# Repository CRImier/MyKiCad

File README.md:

# My KiCad PCBs

This is a repository where I upload [almost] everything that I design in KiCad.
As usual, if you think your work warrants doing backups, just upload it to a git repo ;-P
I hope this will be useful.

About 50% of all of the PCBs have a README describing what they're meant for and
the PCBs physical parameters, the README follows the TEMPLATE.md standard. I'll be
adding more READMEs as I go.

If you need gerbers, you have to plot them yourself by opening the KiCad PCB file
(quick to do with `pcbnew file.kicad_pcb`) and using the File=>Plot dialog.
Majority of the projects already have reasonable export settings, just like I intended.

Same goes for schematic PDFs - if you need them, export them yourself. Adding gerber and sch
files to this repo would be a problem. I might decide to abuse GitHub releases for that eventually,
though.

At some point, hopefully, I'll make a good workflow to also add pictures to READMEs.

Scripts:

- `make_gml.py` - creates .gml files in gerber folders by copying the .gm1 files. Useful for ThisIsNotRocketScience GerberPanelizer.
- `check_kicad5_files.py` - shows you directories which have new Kicad6 kicad_pro and kicad_sch files but still contain old sch and pro files
- `stats.sh` - shows PCB file and README file counts for gamification purposes

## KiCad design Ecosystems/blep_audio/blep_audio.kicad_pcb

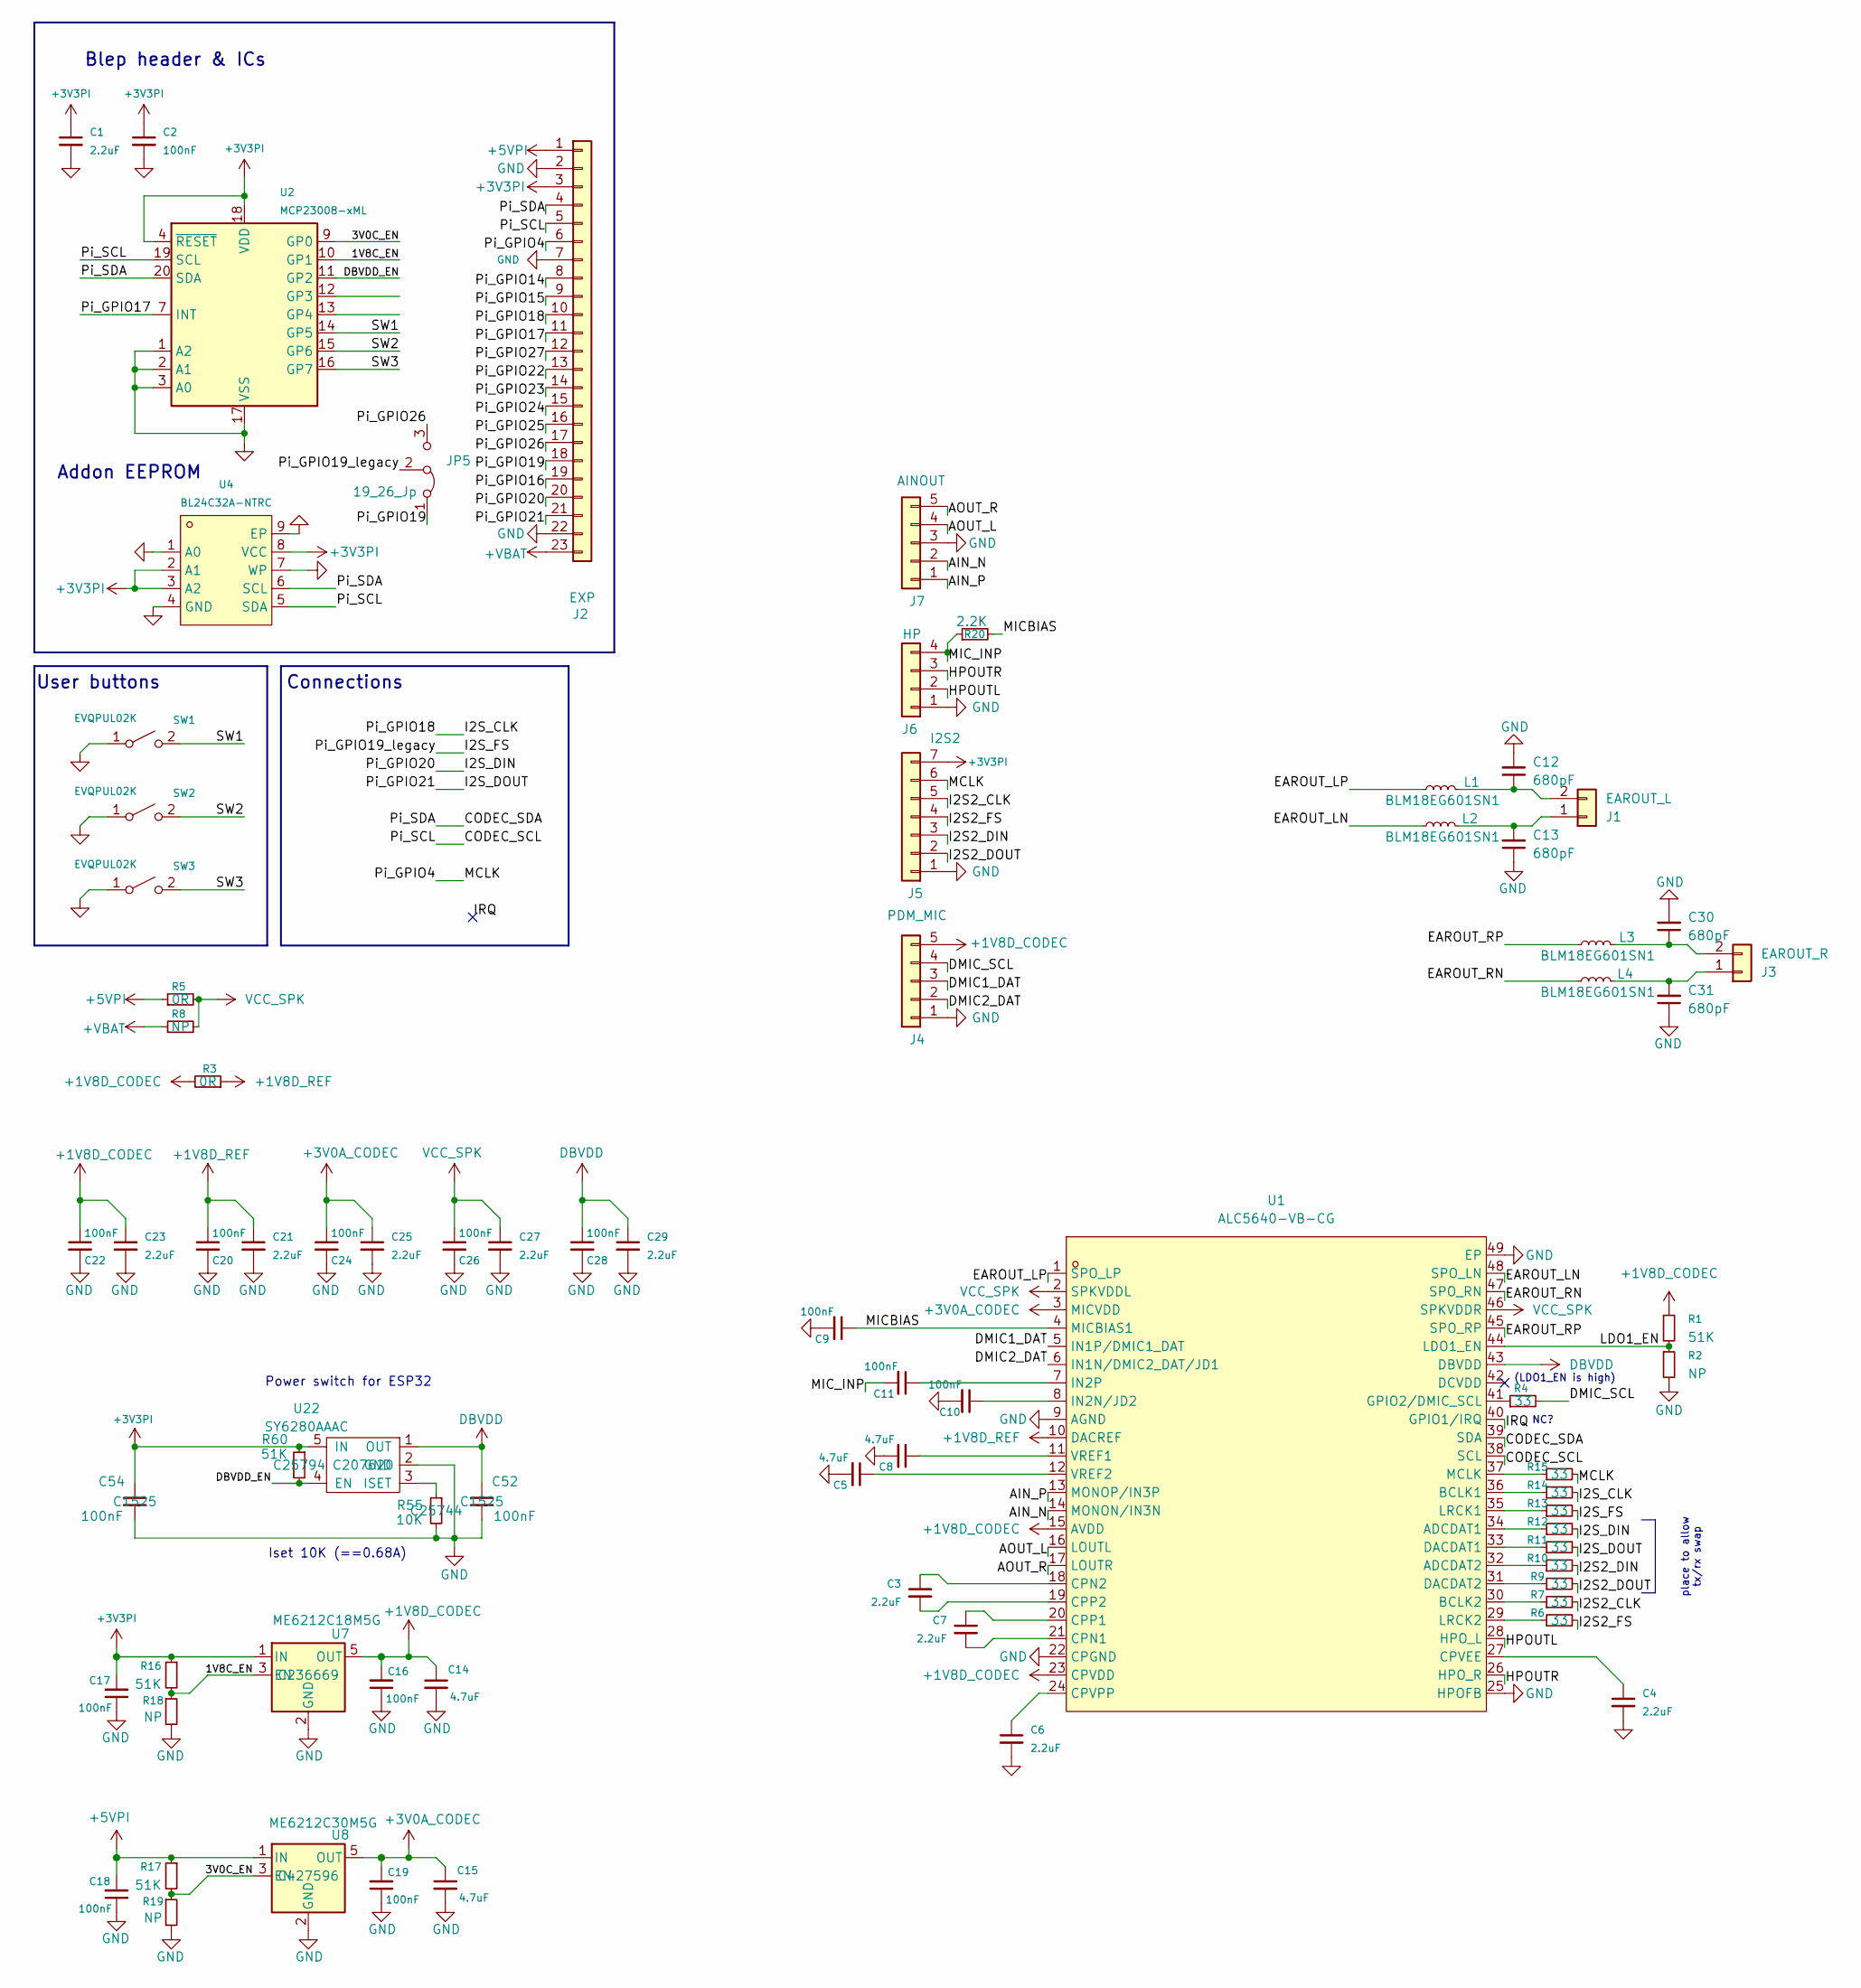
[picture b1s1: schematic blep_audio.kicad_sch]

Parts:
C1, C3, C4, C6, C7, C21, C23, C25, C27, C29: 2.2uF; C_0402_1005Metric
C2, C9, C10, C11, C16, C17, C18, C19, C20, C22, C24, C26, C28: 100nF; C_0402_1005Metric; lcsc_id C1525
C5, C8, C14, C15: 4.7uF; C_0402_1005Metric
C12, C13, C30, C31: 680pF; C_0402_1005Metric
C52, C54: 100nF; C_0402_1005Metric; LCSC Part C1525
J1: EAROUT_L; PinHeader_1x02_P2.54mm_Vertical
J2: EXP; PinHeader_1x23_P2.54mm_Vertical
J3: EAROUT_R; PinHeader_1x02_P2.54mm_Vertical
J4: PDM_MIC; PinHeader_1x05_P2.54mm_Vertical
J5: I2S2; PinHeader_1x07_P2.54mm_Vertical
J6: HP; PinHeader_1x04_P2.54mm_Vertical
J7: AINOUT; PinHeader_1x05_P2.54mm_Vertical
JP5: 19_26_Jp; SolderJumper-3_P1.3mm_Bridged2Bar12_RoundedPad1.0x1.5mm_Num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
L1, L2, L3, L4: BLM18EG601SN1; L_0603_1608Metric
R1, R16, R17: 51K; R_0402_1005Metric
R2, R8, R18, R19: NP; R_0402_1005Metric
R3, R5: 0R; R_0402_1005Metric
R4, R6, R7, R9, R10, R11, R12, R13, R14, R15: 33; R_0402_1005Metric
R20: 2.2K; R_0402_1005Metric
R55: 10K; R_0402_1005Metric; LCSC Part C25744
R60: 51K; R_0402_1005Metric; LCSC Part C25794
SW1, SW2, SW3: EVQPUL02K; Panasonic_EVQPUL_EVQPUC
U1: ALC5640-VB-CG; QFN-48-1EP_6x6mm_P0.4mm_EP4.4x4.4mm; LCSC Part C472491
U2: MCP23008-xML; QFN-20-1EP_4x4mm_P0.5mm_EP2.7x2.7mm
U4: BL24C32A-NTRC; DFN-8_L3.0-W2.0-P0.50-BL-EP; LCSC Part C691878
U7: ME6212C18M5G; SOT-23-5; LCSC Part C236669
U8: ME6212C30M5G; SOT-23-5; LCSC Part C427596
U22: SY6280AAAC; SOT-23-5; LCSC Part C207620

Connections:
+1V8D_CODEC: C14.1, C16.2, C22.1, C23.1, J4.5, R1.1, R3.2, U1.15 (AVDD), U1.23 (CPVDD), U7.5 (OUT)
+1V8D_REF: C20.1, C21.1, R3.1, U1.10 (DACREF)
+3V0A_CODEC: C15.1, C19.2, C24.1, C25.1, U1.3 (MICVDD), U8.5 (OUT)
+3V3PI: C1.1, C2.1, C17.2, C54.1, J2.3, J5.7, R16.1, R60.1, U2.4 (~RESET), U2.18 (VDD), U4.2 (A1), U4.3 (A2), U4.8 (VCC), U7.1 (IN), U22.5 (IN)
+5VPI: C18.2, J2.1, R5.1, R17.1, U8.1 (IN)
+VBAT: J2.23, R8.1
/1V8C_EN: R16.2, R18.1, U2.10 (GP1), U7.3 (EN)
/3V0C_EN: R17.2, R19.1, U2.9 (GP0), U8.3 (EN)
/AIN_N: J7.2, U1.14 (MONON/IN3N)
/AIN_P: J7.1, U1.13 (MONOP/IN3P)
/AOUT_L: J7.4, U1.16 (LOUTL)
/AOUT_R: J7.5, U1.17 (LOUTR)
/CODEC_SCL: J2.5, U1.38 (SCL), U2.19 (SCL), U4.5 (SDA)
/CODEC_SDA: J2.4, U1.39 (SDA), U2.20 (SDA), U4.6 (SCL)
/DBVDD_EN: R60.2, U2.11 (GP2), U22.4 (EN)
/DMIC1_DAT: J4.3, U1.5 (IN1P/DMIC1_DAT)
/DMIC2_DAT: J4.2, U1.6 (IN1N/DMIC2_DAT/JD1)
/DMIC_SCL: J4.4, R4.2
/EAROUT_LN: L2.1, U1.48 (SPO_LN)
/EAROUT_LP: L1.1, U1.1 (SPO_LP)
/EAROUT_RN: L4.1, U1.47 (SPO_RN)
/EAROUT_RP: L3.1, U1.45 (SPO_RP)
/HPOUTL: J6.2, U1.28 (HPO_L)
/HPOUTR: J6.3, U1.26 (HPO_R)
/I2S2_CLK: J5.5, R7.2
/I2S2_DIN: J5.3, R10.2
/I2S2_DOUT: J5.2, R9.2
/I2S2_FS: J5.4, R6.2
/I2S_CLK: J2.10, R14.2
/I2S_DIN: J2.20, R12.2
/I2S_DOUT: J2.21, R11.2
/I2S_FS: JP5.2 (C), R13.2
/IRQ: U1.40 (GPIO1/IRQ)
/LDO1_EN: R1.2, R2.1, U1.44 (LDO1_EN)
/MCLK: J2.6, J5.6, R15.2
/MICBIAS: C9.1, R20.2, U1.4 (MICBIAS1)
/MIC_INP: C11.2, J6.4, R20.1
/Pi_GPIO14: J2.8
/Pi_GPIO15: J2.9
/Pi_GPIO16: J2.19
/Pi_GPIO17: J2.11, U2.7 (INT)
/Pi_GPIO19: J2.18, JP5.1 (A)
/Pi_GPIO22: J2.13
/Pi_GPIO23: J2.14
/Pi_GPIO24: J2.15
/Pi_GPIO25: J2.16
/Pi_GPIO26: J2.17, JP5.3 (B)
/Pi_GPIO27: J2.12
/SW1: SW1.2 (B), U2.14 (GP5)
/SW2: SW2.2 (B), U2.15 (GP6)
/SW3: SW3.2 (B), U2.16 (GP7)
DBVDD: C28.1, C29.1, C52.1, U1.43 (DBVDD), U22.1 (OUT)
GND: C1.2, C2.2, C4.2, C5.2, C6.2, C8.2, C9.2, C10.2, C12.2, C13.1, C14.2, C15.2, C16.1, C17.1, C18.1, C19.1, C20.2, C21.2, C22.2, C23.2, C24.2, C25.2, C26.2, C27.2, C28.2, C29.2, C30.2, C31.1, C52.2, C54.2, J2.2, J2.7, J2.22, J4.1, J5.1, J6.1, J7.3, R2.2, R18.2, R19.2, R55.2, SW1.1 (A), SW2.1 (A), SW3.1 (A), U1.9 (AGND), U1.22 (CPGND), U1.25 (HPOFB), U1.49 (EP), U2.1 (A2), U2.2 (A1), U2.3 (A0), U2.17 (VSS), U4.1 (A0), U4.4 (GND), U4.7 (WP), U4.9 (EP), U7.2 (GND), U8.2 (GND), U22.2 (GND)
unnamed: C13.2, J1.1, L2.2
unnamed: C12.1, J1.2, L1.2
unnamed: C31.2, J3.1, L4.2
unnamed: C30.1, J3.2, L3.2
unnamed: R12.1, U1.34 (ADCDAT1)
unnamed: R10.1, U1.32 (ADCDAT2)
unnamed: R14.1, U1.36 (BCLK1)
unnamed: R7.1, U1.30 (BCLK2)
unnamed: C7.2, U1.21 (CPN1)
unnamed: C3.1, U1.18 (CPN2)
unnamed: C7.1, U1.20 (CPP1)
unnamed: C3.2, U1.19 (CPP2)
unnamed: C4.1, U1.27 (CPVEE)
unnamed: C6.1, U1.24 (CPVPP)
unnamed: R11.1, U1.33 (DACDAT1)
unnamed: R9.1, U1.31 (DACDAT2)
unnamed: R4.1, U1.41 (GPIO2/DMIC_SCL)
unnamed: C10.1, U1.8 (IN2N/JD2)
unnamed: C11.1, U1.7 (IN2P)
unnamed: R13.1, U1.35 (LRCK1)
unnamed: R6.1, U1.29 (LRCK2)
unnamed: R15.1, U1.37 (MCLK)
unnamed: C8.1, U1.11 (VREF1)
unnamed: C5.1, U1.12 (VREF2)
unnamed: R55.1, U22.3 (ISET)
VCC_SPK: C26.1, C27.1, R5.2, R8.2, U1.2 (SPKVDDL), U1.46 (SPKVDDR)

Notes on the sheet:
Addon EEPROM
place to allow tx/rx swap
Power switch for ESP32
Connections
NC?
User buttons
Blep header & ICs
Iset 10K (==0.68A)
(LDO1_EN is high)

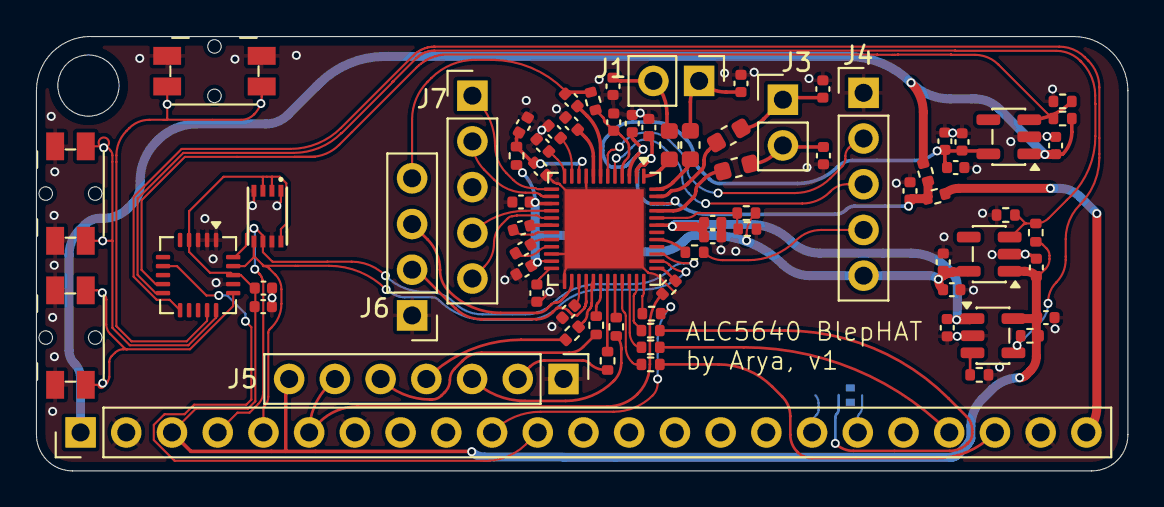
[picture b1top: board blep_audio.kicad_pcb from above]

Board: 2 copper layers, 60.6 x 24.1 mm, 76 parts (1 on the bottom side), 70 nets.

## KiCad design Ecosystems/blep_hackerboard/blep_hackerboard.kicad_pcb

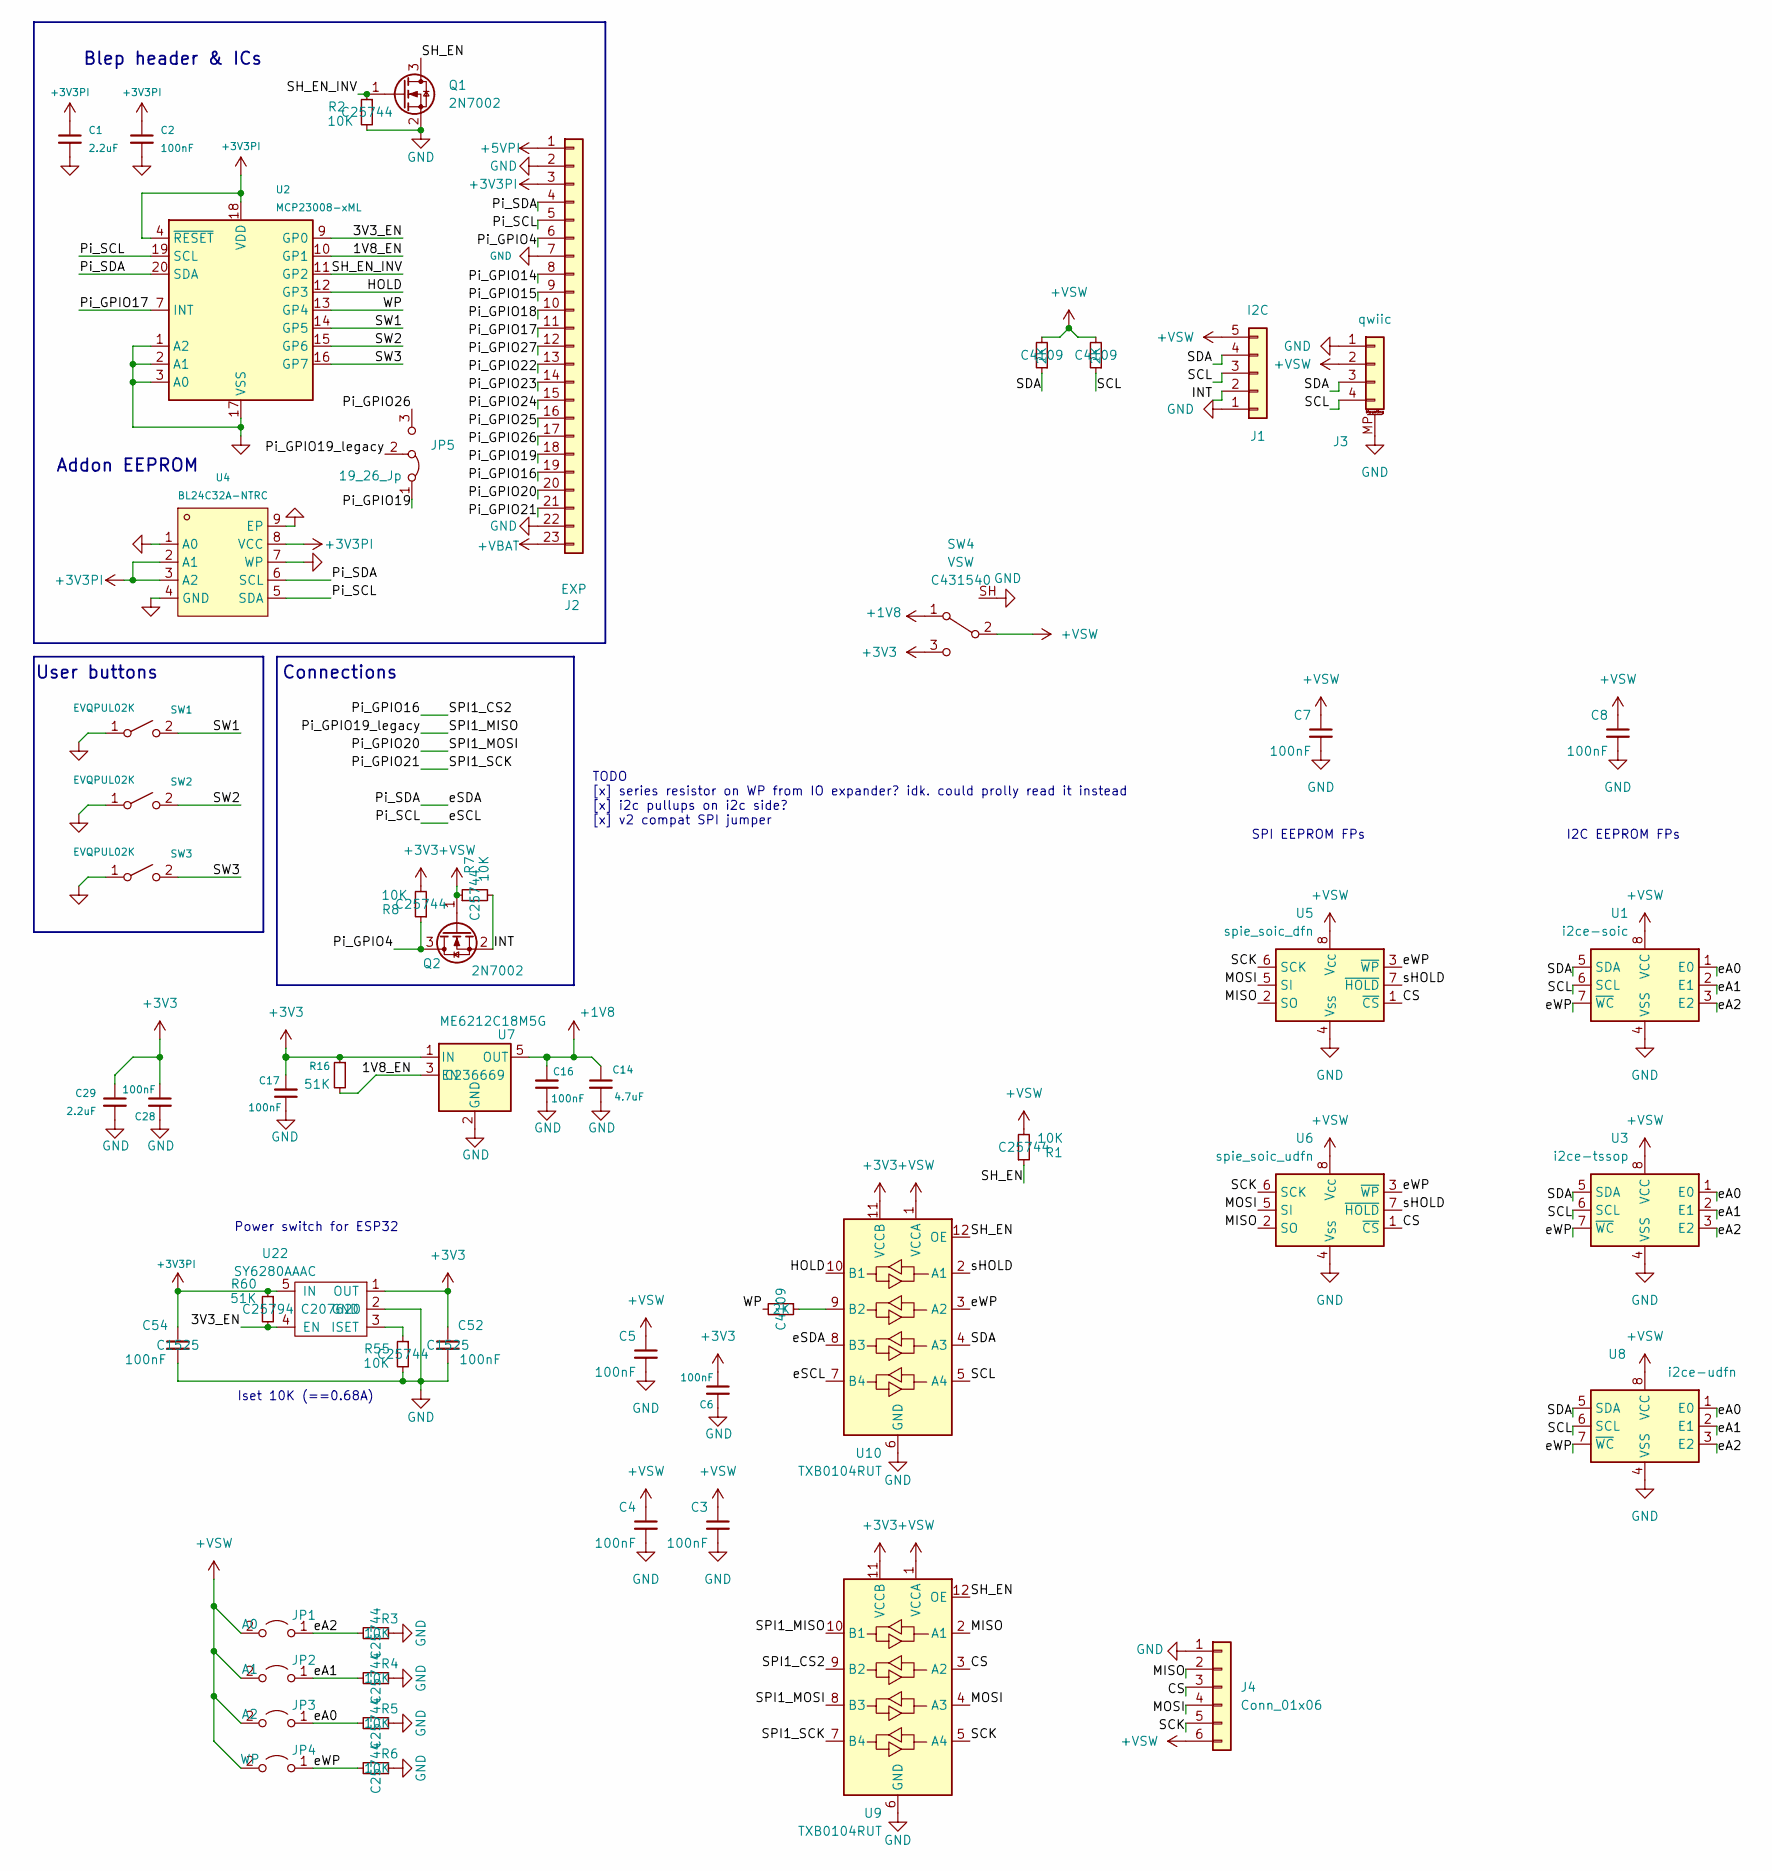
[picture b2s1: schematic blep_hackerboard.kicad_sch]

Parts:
C1, C29: 2.2uF; C_0402_1005Metric
C2, C3, C4, C5, C6, C7, C8, C16, C17, C28: 100nF; C_0402_1005Metric; lcsc_id C1525
C14: 4.7uF; C_0402_1005Metric
C52, C54: 100nF; C_0402_1005Metric; LCSC Part C1525
J1: I2C; PinHeader_1x05_P2.54mm_Vertical
J2: EXP; PinHeader_1x23_P2.54mm_Vertical
J3: qwiic; JST_SH_SM04B-SRSS-TB_1x04-1MP_P1.00mm_Horizontal
J4: Conn_01x06; PinHeader_1x06_P2.54mm_Vertical
JP1: A0; jumper_smol
JP2: A1; jumper_smol
JP3: A2; jumper_smol
JP4: WP; jumper_smol
JP5: 19_26_Jp; SolderJumper-3_P1.3mm_Bridged2Bar12_RoundedPad1.0x1.5mm_Num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
Q1, Q2: 2N7002; SOT-23
R1, R2, R3, R4, R5, R6, R7, R8, R55: 10K; R_0402_1005Metric; LCSC Part C25744
R9, R10, R116: 2K; R_0402_1005Metric; LCSC Part C4109
R16: 51K; R_0402_1005Metric
R60: 51K; R_0402_1005Metric; LCSC Part C25794
SW1, SW2, SW3: EVQPUL02K; Panasonic_EVQPUL_EVQPUC
SW4: VSW; SW_SPDT_PCM12_SH; LCSC Part C431540
U1: i2ce-soic; SOIC-8_3.9x4.9mm_P1.27mm
U2: MCP23008-xML; QFN-20-1EP_4x4mm_P0.5mm_EP2.7x2.7mm
U3: i2ce-tssop; TSSOP-8_4.4x3mm_P0.65mm
U4: BL24C32A-NTRC; DFN-8_L3.0-W2.0-P0.50-BL-EP; LCSC Part C691878
U5: spie_soic_dfn; SOIC-8W_5.3x5.3mm_P1.27mm
U6: spie_soic_udfn; DFN-8-1EP_3x2mm_P0.5mm_EP1.3x1.5mm
U7: ME6212C18M5G; SOT-23-5; LCSC Part C236669
U8: i2ce-udfn; DFN-8-1EP_3x2mm_P0.5mm_EP1.3x1.5mm
U9, U10: TXB0104RUT; Texas_R-PUQFN-N12
U22: SY6280AAAC; SOT-23-5; LCSC Part C207620

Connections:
+1V8: C14.1, C16.2, SW4.1 (A), U7.5 (OUT)
+3V3: C6.1, C17.2, C28.1, C29.1, C52.1, R8.2, R16.1, SW4.3 (C), U7.1 (IN), U9.11 (VCCB), U10.11 (VCCB), U22.1 (OUT)
+3V3PI: C1.1, C2.1, C54.1, J2.3, R60.1, U2.4 (~RESET), U2.18 (VDD), U4.2 (A1), U4.3 (A2), U4.8 (VCC), U22.5 (IN)
+5VPI: J2.1
+VBAT: J2.23
+VSW: C3.1, C4.1, C5.1, C7.1, C8.1, J1.5, J3.2, J4.6, JP1.2 (B), JP2.2 (B), JP3.2 (B), JP4.2 (B), Q2.1 (G), R1.2, R7.1, R9.2, R116.2, SW4.2 (B), U1.8 (VCC), U3.8 (VCC), U5.8 (V_{CC}), U6.8 (V_{CC}), U8.8 (VCC), U9.1 (VCCA), U10.1 (VCCA)
/1V8_EN: R16.2, U2.10 (GP1), U7.3 (EN)
/3V3_EN: R60.2, U2.9 (GP0), U22.4 (EN)
/CS: J4.3, U5.1 (~CS), U6.1 (~CS), U9.3 (A2)
/HOLD: U2.12 (GP3), U10.10 (B1)
/INT: J1.2, Q2.2 (S), R7.2
/MISO: J4.2, U5.2 (SO), U6.2 (SO), U9.2 (A1)
/MOSI: J4.4, U5.5 (SI), U6.5 (SI), U9.4 (A3)
/Pi_GPIO4: J2.6, Q2.3 (D), R8.1
/Pi_GPIO14: J2.8
/Pi_GPIO15: J2.9
/Pi_GPIO16: J2.19, U9.9 (B2)
/Pi_GPIO17: J2.11, U2.7 (INT)
/Pi_GPIO18: J2.10
/Pi_GPIO19: J2.18, JP5.1 (A)
/Pi_GPIO19_legacy: JP5.2 (C), U9.10 (B1)
/Pi_GPIO20: J2.20, U9.8 (B3)
/Pi_GPIO21: J2.21, U9.7 (B4)
/Pi_GPIO22: J2.13
/Pi_GPIO23: J2.14
/Pi_GPIO24: J2.15
/Pi_GPIO25: J2.16
/Pi_GPIO26: J2.17, JP5.3 (B)
/Pi_GPIO27: J2.12
/Pi_SCL: J2.5, U2.19 (SCL), U4.5 (SDA), U10.7 (B4)
/Pi_SDA: J2.4, U2.20 (SDA), U4.6 (SCL), U10.8 (B3)
/SCK: J4.5, U5.6 (SCK), U6.6 (SCK), U9.5 (A4)
/SCL: J1.3, J3.4, R9.1, U1.6 (SCL), U3.6 (SCL), U8.6 (SCL), U10.5 (A4)
/SDA: J1.4, J3.3, R116.1, U1.5 (SDA), U3.5 (SDA), U8.5 (SDA), U10.4 (A3)
/SH_EN: Q1.3 (D), R1.1, U9.12 (OE), U10.12 (OE)
/SH_EN_INV: Q1.1 (G), R2.1, U2.11 (GP2)
/SW1: SW1.2 (B), U2.14 (GP5)
/SW2: SW2.2 (B), U2.15 (GP6)
/SW3: SW3.2 (B), U2.16 (GP7)
/WP: R10.2, U2.13 (GP4)
/eA0: JP3.1 (A), R5.2, U1.1 (E0), U3.1 (E0), U8.1 (E0)
/eA1: JP2.1 (A), R4.2, U1.2 (E1), U3.2 (E1), U8.2 (E1)
/eA2: JP1.1 (A), R3.2, U1.3 (E2), U3.3 (E2), U8.3 (E2)
/eWP: JP4.1 (A), R6.2, U1.7 (~WC), U3.7 (~WC), U5.3 (~WP), U6.3 (~WP), U8.7 (~WC), U10.3 (A2)
/sHOLD: U5.7 (~HOLD), U6.7 (~HOLD), U10.2 (A1)
GND: C1.2, C2.2, C3.2, C4.2, C5.2, C6.2, C7.2, C8.2, C14.2, C16.1, C17.1, C28.2, C29.2, C52.2, C54.2, J1.1, J2.2, J2.7, J2.22, J3.1, J3.MP (MountPin), J4.1, Q1.2 (S), R2.2, R3.1, R4.1, R5.1, R6.1, R55.2, SW1.1 (A), SW2.1 (A), SW3.1 (A), SW4.SH, U1.4 (VSS), U2.1 (A2), U2.2 (A1), U2.3 (A0), U2.17 (VSS), U3.4 (VSS), U4.1 (A0), U4.4 (GND), U4.7 (WP), U4.9 (EP), U5.4 (V_{SS}), U6.4 (V_{SS}), U7.2 (GND), U8.4 (VSS), U9.6 (GND), U10.6 (GND), U22.2 (GND)
unnamed: R10.1, U10.9 (B2)
unnamed: R55.1, U22.3 (ISET)

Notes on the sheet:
Iset 10K (==0.68A)
Addon EEPROM
Power switch for ESP32
I2C EEPROM FPs
SPI EEPROM FPs
Connections
User buttons
TODO [x] series resistor on WP from IO expander? idk. could prolly read it instead [x] i2c pullups on i2c side? [x] v2 compat SPI jumper
Blep header & ICs

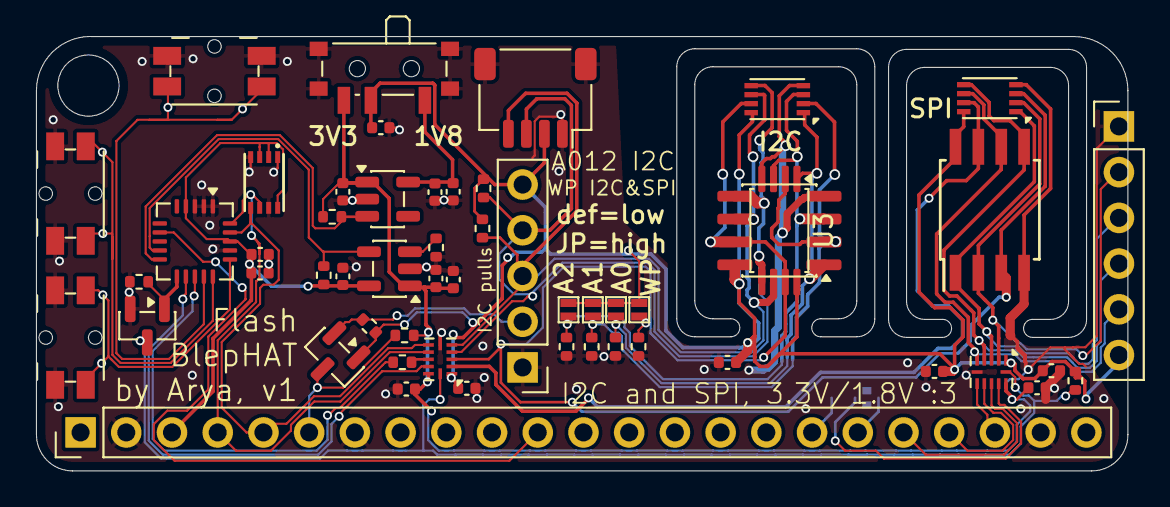
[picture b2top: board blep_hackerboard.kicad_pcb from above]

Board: 2 copper layers, 60.6 x 24.1 mm, 55 parts (1 on the bottom side), 38 nets.

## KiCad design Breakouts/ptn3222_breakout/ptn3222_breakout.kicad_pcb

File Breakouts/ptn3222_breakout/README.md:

# PTN3222 breakout

This is a breakout for the PTN3222, eUSB2 to USB2 converter and redriver chip, exposing as many of its features as possible
in the smallest possible footprint. PTN3222 can work in either of the two roles, with eUSB2 either facing host or device ports.
This board is designed to help you make use of any cool eUSB2 tech you might encounter in the future.

The PTN3222 is used for seemingly being the best bang for your buck, and being configurable without resistors.
TUSB2E22 is quite expensive and more bothersome to wireup,
and CYUSB2405 is apparently unobtainium; plus, both of these chips are dual-port.

All relevant pins are exposed on JST-SH connectors with QWIIC-style pinout, for ease of wireup.
All pinouts are silkscreened on the PCB, so you can wire it up manually if you wish, too.

I2C configuration should not be required for functioning in either of the two USB roles (datasheet page 10, at the top).
So, if you don't need I2C, feel free to omit R2, R4, Q1, and J3. That said, it's not clear to me that you can
safely omit R5 and R3 - watch out.

The board includes 5.1k pullups on the QWIIC I2C port, marked as R2 and R4.
I2C is translated to 3.3V by default, since the PTN3222 I2C port needs 1.8V from what I can tell,
and QWIIC standard requires 3.3V I2C.

PTN3222 ADDR is pulled to 1.8V with a 56k resistor. This should result in I2C address 0x47 (datasheet page 8).
Short JP1 to switch address to 0x4f, or short R1 to switch address to 0x43.

eUSB2's JST-SH connector's VCC pin is disconnected by default. This is done to avoid supplying 3.3V into 1.8V if eUSB and USB connectors
are mixed up, and also avoid accidentally supplying voltage into an eUSB2-carrying circuit without checking that the system can handle that voltage.
Solder the port's VCC switch jumper into your preferred position according to the system you'll use it in, or, alternatively, don't solder it at all.

eUSB2 and USB2 lines are not impedance-matched - this is a 2-layer board, USB2 is pretty robust, and the on-board distances are short.
They are, however, mostly skew-matched. USB2 and eUSB2 lines are ESD-protected by U3 (optional).

The USB-C port is not required for functioning. If you don't need it, feel free to DNP J4, R6-R9, as well as U4, C7, C8 (5V->3V3 reg).

If you know any other cool eUSB2 chips, please contact me and let me know!

## Images

## Notes

- Signal names are silkscreened on the board, top and bottom layers.
- This board is untested and there's no guarantees of fitness.
- I recommend a stencil for assembling this board.

## Info

- Software: Kicad 9
- Version: 1
- PCB size: 32x14mm
- Layer count: 2

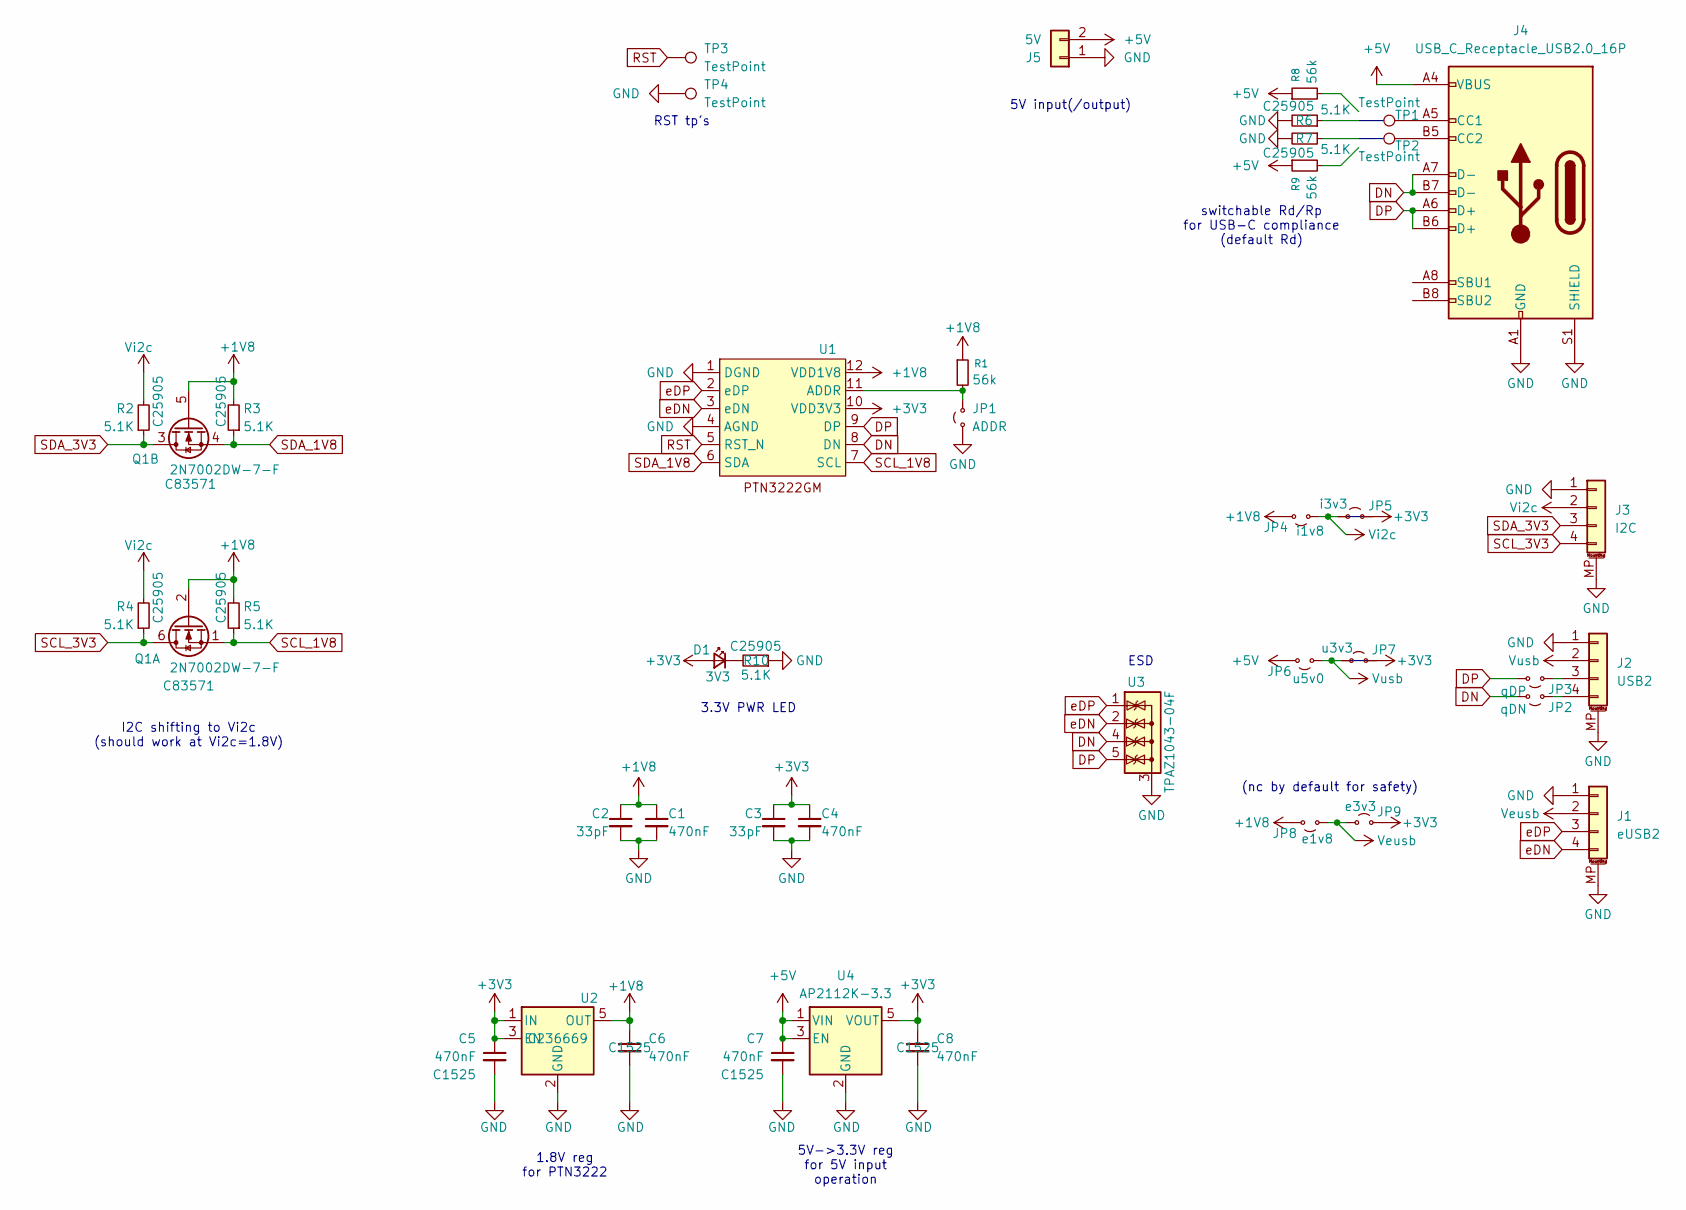
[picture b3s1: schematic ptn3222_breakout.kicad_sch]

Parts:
C1, C4: 470nF; C_0402_1005Metric
C2, C3: 33pF; C_0402_1005Metric
C5, C6, C7, C8: 470nF; C_0402_1005Metric; LCSC Part C1525
D1: 3V3; LED_0603_1608Metric
J1: eUSB2; JST_SH_SM04B-SRSS-TB_1x04-1MP_P1.00mm_Horizontal
J2: USB2; JST_SH_SM04B-SRSS-TB_1x04-1MP_P1.00mm_Horizontal
J3: I2C; JST_SH_SM04B-SRSS-TB_1x04-1MP_P1.00mm_Horizontal
J4: USB_C_Receptacle_USB2.0_16P; USB_C_Receptacle_HRO_TYPE-C-31-M-12
J5: 5V; PinHeader_1x02_P2.54mm_Vertical
JP1: ADDR; small_jumper
JP2: qDN; small_jumper
JP3: qDP; small_jumper
JP4: i1v8; small_jumper
JP5: i3v3; small_jumper
JP6: u5v0; small_jumper
JP7: u3v3; small_jumper
JP8: e1v8; small_jumper
JP9: e3v3; small_jumper
Q1: 2N7002DW-7-F; SOT-363_SC-70-6; LCSC Part C83571
R1, R8, R9: 56k; R_0402_1005Metric
R2, R3, R4, R5, R6, R7, R10: 5.1K; R_0402_1005Metric; LCSC Part C25905
TP1, TP2, TP3, TP4: TestPoint; small_tp
U1: XQFN-12_2x2mm_P0.4mm
U2: ME6212C18M5G; SOT-23-5; LCSC Part C236669
U3: TPAZ1043-04F; USON-10_2.5x1.0mm_P0.5mm
U4: AP2112K-3.3; SOT-23-5

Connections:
+1V8: C1.1, C2.1, C6.1, JP4.2 (B), JP8.2 (B), Q1.2 (G), Q1.5 (G), R1.1, R3.2, R5.2, U1.12 (VDD1V8), U2.5 (OUT)
+3V3: C3.1, C4.1, C5.1, C8.1, D1.2 (A), JP5.2 (B), JP7.2 (B), JP9.2 (B), U1.10 (VDD3V3), U2.1 (IN), U2.3 (EN), U4.5 (VOUT)
+5V: C7.1, J4.A4 (VBUS), J4.A9 (VBUS), J4.B4 (VBUS), J4.B9 (VBUS), J5.2, JP6.2 (B), R8.1, R9.1, U4.1 (VIN), U4.3 (EN)
DN: J4.A7 (D-), J4.B7 (D-), JP2.1 (A), U1.8 (DN), U3.4 (IO3), U3.7 (NC)
DP: J4.A6 (D+), J4.B6 (D+), JP3.1 (A), U1.9 (DP), U3.5 (IO4), U3.6 (NC)
GND: C1.2, C2.2, C3.2, C4.2, C5.2, C6.2, C7.2, C8.2, J1.1, J1.MP (MountPin), J2.1, J2.MP (MountPin), J3.1, J3.MP (MountPin), J4.A1 (GND), J4.A12 (GND), J4.B1 (GND), J4.B12 (GND), J4.S1 (SHIELD), J5.1, JP1.1 (A), R6.2, R7.2, R10.1, TP4.1, U1.1 (DGND), U1.4 (AGND), U2.2 (GND), U3.3 (G), U3.8 (G), U4.2 (GND)
unnamed: D1.1 (K), R10.2
unnamed: J2.3, JP3.2 (B)
unnamed: J2.4, JP2.2 (B)
unnamed: J4.A5 (CC1), TP1.1
unnamed: J4.B5 (CC2), TP2.1
unnamed: JP1.2 (B), R1.2, U1.11 (ADDR)
RST: TP3.1, U1.5 (RST_N)
SCL_1V8: Q1.1 (S), R5.1, U1.7 (SCL)
SCL_3V3: J3.4, Q1.6 (D), R4.1
SDA_1V8: Q1.4 (S), R3.1, U1.6 (SDA)
SDA_3V3: J3.3, Q1.3 (D), R2.1
Veusb: J1.2, JP8.1 (A), JP9.1 (A)
Vi2c: J3.2, JP4.1 (A), JP5.1 (A), R2.2, R4.2
Vusb: J2.2, JP6.1 (A), JP7.1 (A)
eDN: J1.4, U1.3 (eDN), U3.2 (IO2), U3.9 (NC)
eDP: J1.3, U1.2 (eDP), U3.1 (IO1), U3.10 (NC)

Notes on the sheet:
I2C shifting to Vi2c (should work at Vi2c=1.8V)
switchable Rd/Rp for USB-C compliance (default Rd)
1.8V reg for PTN3222
ESD
RST tp's
(nc by default for safety)
3.3V PWR LED
5V input(/output)
5V->3.3V reg for 5V input operation

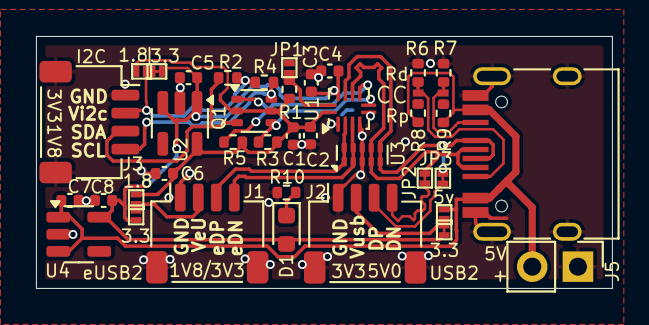
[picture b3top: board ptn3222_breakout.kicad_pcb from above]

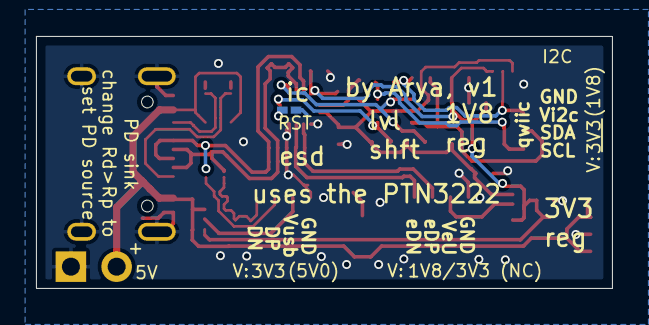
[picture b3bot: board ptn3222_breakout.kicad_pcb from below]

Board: 2 copper layers, 32.0 x 14.0 mm, 42 parts (2 on the bottom side), 22 nets.
